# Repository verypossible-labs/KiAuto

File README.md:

KiAuto
======

KiCad automation scripts.
In particular to automate tasks that can't be done using the KiCad native Python interface.
The automation is carried out emulating the user interaction.

## Index

* [Introduction](#introduction)
* [Installation](#installation)
  * [Dependencies](#dependencies)
  * [No installation](#no-installation)
  * [Installation using pip](#installation-using-pip)
  * [Python style installation](#python-style-installation)
  * [Installation on Ubuntu/Debian](#installation-on-debian)
* [Usage](#usage)
  * [Export a schematic to PDF or SVG](#export-a-schematic-to-pdf-or-svg)
  * [Run ERC](#run-erc)
  * [Generate netlist](#generate-netlist)
  * [Update BoM XML or basic BoM generation](#update-bom-xml-or-basic-bom-generation)
  * [Run DRC](#run-drc)
  * [Export layout as PDF](#export-layout-as-pdf)
  * [Refilling copper zones](#refilling-copper-zones)
  * [Common options](#common-options)
  * [Ignoring warnings and errors from ERC or DRC](#ignoring-warnings-and-errors-from-erc-or-drc)
* [History](#history)

## Introduction

Current implementation uses a virtual X server ([xvfb](https://www.x.org/releases/X11R7.6/doc/man/man1/Xvfb.1.xhtml)),
sends key events and detects which window is focused using [xdotool](https://github.com/jordansissel/xdotool/)
and handles the clipboard using [xclip](https://github.com/astrand/xclip).
This means it works for Linux. KiCad is also available for Windows and MacOSX, help to port the scripts will be appreciated.

Currently tested and working:

- Exporting schematics to PDF, SVG, PS, DXF and HPGL
- Exporting layouts (PCBs) to PDF
- Running ERC on schematics
- Running DRC on layouts
- Netlist generation
- Basic BoM generation (mainly the XML needed for [KiBoM](https://github.com/SchrodingersGat/KiBoM))

If you are looking for Gerbers, Drill, Position, STEP and more take a look at [KiBot](https://github.com/INTI-CMNB/KiBot).

This project started as a fork of [kicad-automation-scripts](https://github.com/obra/kicad-automation-scripts) for more information read the [history](#History) section.

A docker image containg the scripts and other tools can be found at [DockerHub](https://hub.docker.com/repository/docker/setsoft/kicad_auto).

## Installation

### Dependencies

If you are installing from a Debian package you don't need to worry about dependencies, otherwise you need to install:

- [**KiCad**](http://kicad-pcb.org/) 5.1.x
- [**xdotool**](https://github.com/jordansissel/xdotool)
- [**xclip**](https://github.com/astrand/xclip)
- [**xsltproc**](http://xmlsoft.org/xslt/) (usually installed as a KiCad dependency). Only needed for BoMs.

If you want to debug problems you could also need:

- [**recordmydesktop**](http://recordmydesktop.sourceforge.net/about.php), to create a video of the KiCad session.
- [**x11vnc**](http://www.karlrunge.com/x11vnc/) and a client like [**ssvnc**](http://www.karlrunge.com/x11vnc/ssvnc.html), to see the KiCad live interaction.
- [**fluxbox**](http://fluxbox.org/) and [**wmctrl**](http://tripie.sweb.cz/utils/wmctrl/) if you want to have a window manager when using **x11vnc**. Othewise windows can't be moved.

### Installation using pip

```shell
pip install kiauto
```

You can also install the current git code running:

```shell
pip install .
```

In the root of the repo.

### Python style installation

Just run the setup, like with any other Python tool:

```
sudo python3 setup.py install
```

### No installation

You can use the scripts without installing. The scripts are located at the *src/* directory.

You can also define bash aliases:

```
alias pcbnew_do=PATH_TO_REPO/src/pcbnew_do
alias eeschema_do=PATH_TO_REPO/src/eeschema_do
```

Note that the following Python 3 packages must be installed:

- [**xvfbwrapper**](https://pypi.org/project/xvfbwrapper/)
- [**psutil**](https://pypi.org/project/psutil/)

Also note that this won't work if you plan to call the scripts from KiBot or other tool.
Aliases are good for direct command line use, but are restricted to the shell where the aliases are declared.
You can add the aliases to the bash configuration, but if the tool doesn't use bash or don't even use a shell this won't work.

### Installation on Debian

Get the Debian package from the [releases section](https://github.com/INTI-CMNB/KiAuto/releases) and run:
```
sudo apt install ./kiauto_*_all.deb
```

## Usage

Two scripts are provided:

- **eeschema_do**: interacts with KiCad's eeschema (schematic editor)
- **pcbnew_do**: interacts with KiCad's pcbnew (PCB editor)

You can get detailed help using the *--help* command line option. Here I include some basic usage.

### Export a schematic to PDF or SVG

```
eeschema_do export -a YOUR_SCHEMATIC.sch DESTINATION/
```
This will create *DESTINATION/YOUR_SCHEMATIC.pdf* file containing all the schematic pages. If you want just one page remove the *-a* option. If you want an SVG file just use *-f svg* like this:
```
eeschema_do export -a -f svg YOUR_SCHEMATIC.sch DESTINATION/
```
In this case you'll get one SVG for each page in your schematic.

### Run ERC

To run the Electrical Rules Check:
```
eeschema_do run_erc YOUR_SCHEMATIC.sch DESTINATION/
```
If an error is detected you'll get a message and the script will return a negative error level. Additionally you'll get *DESTINATION/YOUR_SCHEMATIC.erc* containing KiCad's report.

### Generate netlist

To generate or update the netlist, needed by other tools:
``` 
eeschema_do netlist YOUR_SCHEMATIC.sch DESTINATION/
```
You'll get *DESTINATION/YOUR_SCHEMATIC.net*

### Update BoM XML or basic BoM generation:

Tools like [KiBoM](https://github.com/SchrodingersGat/KiBoM) can generate a nice BoM, but in order to run them from the command line you need to be sure that the project's XML BoM is updated. You can do it running:
``` 
eeschema_do bom_xml YOUR_SCHEMATIC.sch DESTINATION/
```
After running it *./YOUR_SCHEMATIC.xml* will be updated. You'll also get *DESTINATION/YOUR_SCHEMATIC.csv* contain a very basic BoM generated using KiCad's *bom2grouped_csv.xsl* template.

### Run DRC

To run the Distance Rules Check:
```
pcbnew_do run_drc YOUR_PCB.kicad_pcb DESTINATION/
```
If an error is detected you'll get a message and the script will return a negative error level. Additionally you'll get *DESTINATION/drc_result.rpt* containing KiCad's report. You can select the name of the report using *--output_name* and you can ignore unconneted nets using *--ignore_unconnected*.

### Export layout as PDF

This is useful to complement your gerber files including some extra information in the *Dwgs.User* or *Cmts.User* layer.
```
pcbnew_do export YOUR_PCB.kicad_pcb DESTINATION/ LAYER1 LAYER2
```
Will generate *DESTINATION/printed.pdf* containing LAYER1 and LAYER2 overlapped. You can list as many layers as you want. I use things like ```F.Cu Dwgs.User```. The name of the layers is the same you see in the GUI, if your first inner layer is GND you just need to use ```GND.Cu```.

If you need to get a list of valid layers run:

```
pcbnew_do export --list YOUR_PCB.kicad_pcb
```

### Refilling copper zones

When you run the DRC KiCad will refill all zones. If you didn't do it before saving it could lead to a situation where the PCB that passes DRC isn't the one saved to disk. To solve you can use *-s* option to save the PCB after DRC:

```
pcbnew_do run_drc -s YOUR_PCB.kicad_pcb DESTINATION/
```

Another option could be to avoid changing the file on disk, but fill the zones before printing. To achieve it you can invoke the export command like this:

```
pcbnew_do export -f YOUR_PCB.kicad_pcb DESTINATION/ LAYERs...
```

### Common options

By default all the scripts run very quiet. If you want to get some information about what's going on use *-v*. 

The nature of these scripts make them very fragile. In particular when you run them in your every day desktop. You must avoid having *eeschema* and/or *pcbnew* windows opened while running the scripts. If you need to debug a problem you can:
1. Use the *-vv* option to get debug information
2. Use the *-r* option to record a video (OGV format) containing the GUI session. The file will be stored in the output directory and its name will begin with the name of the requested command.
3. Use the *-s* and *-w* options to start **x11vnc**. The execution will stop asking for a keypress. At this time you can start a VNC client like this: ```ssvncviewer :0```. You'll be able to see KiCad running and also interact with it.
4. Same as 3 but also using *-m*, in this case you'll get a window manager to move the windows and other stuff.

### Ignoring warnings and errors from ERC or DRC

Sometimes we need to ignore some warnings and/or errors reported during the ERC and/or DRC test.

To achieve it you need to create a *filters file*. Each line contains a rule to exclude one or more matching errors. The syntax is:

```
ERROR_NUMBER,REGULAR_EXPRESSION
```

The regular expression must follow the Python syntax. In the simplest case this can be just the text that the error must contain.

The error number is just the KiCad internal number for the error you want to ignore.

Here is an example, suppose our report says:

```
** Created on 2020-06-05 11:16:21 **

** Found 2 DRC errors **
ErrType(45): Courtyards overlap
    @(144.361 mm, 101.752 mm): Footprint C16 on F.Cu
    @(144.825 mm, 101.244 mm): Footprint C19 on F.Cu
ErrType(45): Courtyards overlap
    @(159.885 mm, 97.663 mm): Footprint R4 on F.Cu
    @(160.393 mm, 97.191 mm): Footprint C21 on F.Cu

** Found 0 unconnected pads **

** End of Report **
```

Here we have two errors, both number 45. So lets suppose we want to ignore the first error, we could use the following filter:

```
45,Footprint C16
```

This will ignore any error of type 45 (Courtyards overlap) related to *Footprint C16*. To use
it you just need mto use the *-f* command line option:

```
pcbnew_do run_drc -f FILTER_FILE YOUR_PCB.kicad_pcb DESTINATION/
```

Note that when using KiCad 6 the errors are strings enclosed by brackets, use only the text, not the brackets.

## History

I saw a presentation of Jesse Vincent ([@obra](https://github.com/obra)) in the [KiCon 2019](https://2019.kicad-kicon.com/) about automating KiCad tasks.

The presentation used [kicad-automation-scripts](https://github.com/obra/kicad-automation-scripts) as base for the tasks that needs to emulate the user interaction.
So I forked this repo.

But this wasn't the original repo, Jesse's repo is a fork of Productize SPRL's [scripts](https://github.com/productize/kicad-automation-scripts).
These scripts were created by Seppe Stas ([@seppestas](https://github.com/seppestas)).

According to Seppe he took many ideas from the [split-flap display project](https://scottbez1.github.io/splitflap/).
In particular from the files [here](https://github.com/scottbez1/splitflap/tree/master/electronics/scripts).
The author of split-flap is Scott Bezek ([@scottbez1](https://github.com/scottbez1)).
Scott explained the idea in his [blog](https://scottbezek.blogspot.be/2016/04/scripting-kicad-pcbnew-exports.html)

So this is the history of the scripts, at least what I know. In short: Scott Bezek had the original idea and used it for his project, but not as a separated tool.
Seppe Stas from Productize SPRL took the scripts and created a tool from them.
Then Jesse Vincent used the scripts to create a bigger set of tools and presented it on KiCon 2019.
And finally I (Salvador E. Tropea) took Jesse's scripts and adapted them to the needs of [KiBot](https://github.com/INTI-CMNB/KiBot).

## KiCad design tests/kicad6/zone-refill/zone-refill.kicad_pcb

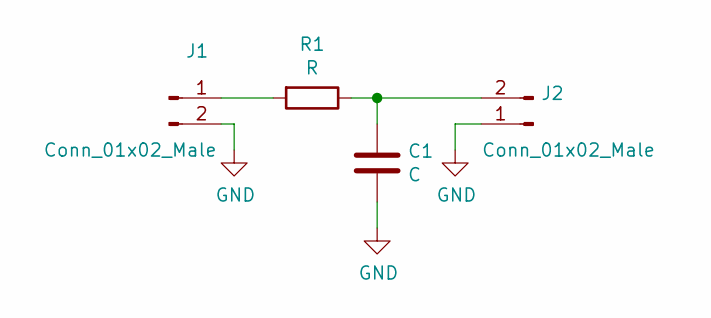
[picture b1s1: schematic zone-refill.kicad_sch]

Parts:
C1: C; C_0805_2012Metric
J1, J2: Conn_01x02_Male; PinHeader_1x02_P2.54mm_Vertical
R1: R; R_0805_2012Metric

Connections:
GND: C1.2, J1.2, J2.1
unnamed: C1.1, J2.2, R1.1
unnamed: J1.1, R1.2

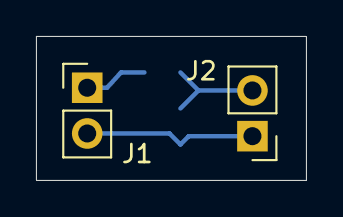
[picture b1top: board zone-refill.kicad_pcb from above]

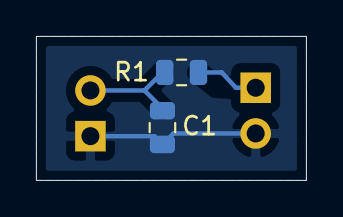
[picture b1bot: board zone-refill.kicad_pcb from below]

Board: 2 copper layers, 15.0 x 8.0 mm, 4 parts (2 on the bottom side), 3 nets.

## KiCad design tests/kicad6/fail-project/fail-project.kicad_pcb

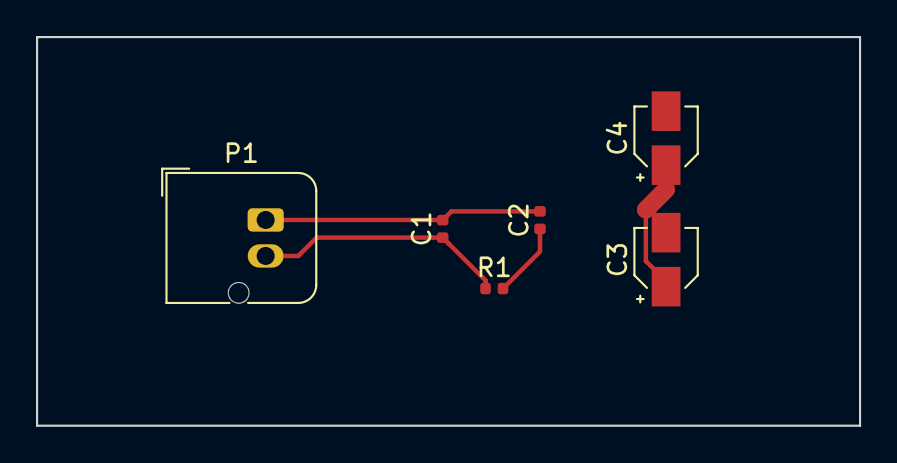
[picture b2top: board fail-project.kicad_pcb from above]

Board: 2 copper layers, 45.7 x 21.6 mm, 6 parts (0 on the bottom side), 5 nets.

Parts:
C1, C2: C; C_0402_1005Metric
C3, C4: CP; CP_Elec_3x5.3
P1: CONN_01X02; JST_JWPF_B02B-JWPF-SK-R_1x02_P2.00mm_Vertical
R1: R; R_0402_1005Metric

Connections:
/Power/VCC: C1.1, P1.2, R1.1
GND: C1.2, C2.2, P1.1
unnamed: C2.1, R1.2
unnamed: C3.1, C4.1
unnamed: C3.2, C4.2

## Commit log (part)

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2019-04-10 Disable the "rescue" dialog on schematic open
2019-04-10 Switch to building our Dockerfile directly, rather than using productize' intermediate version
2019-04-10 switch to the current way to trigger plotting "Alt-f l"
2019-04-10 Update Dockerfile to include license and content from the previous intermediate Dockerfile
2019-04-10 port schematic output to KiCAD 5.1
2019-04-11 A first pass at a working BOM generator
2019-04-18 reorder the library warning to later, since that's whne it seems to run
2020-03-04 Modified to be run outside docker: 1) Language set as english + UTF-8 2) Saves the current pcbnew config and creates one usable. Te original is restored.
2020-03-04 util/ui_automation.py: - recorded_xvfb now can be used without recording - added wait_focused and wait_not_focused - added slip_id parameter to wait_for_window to differentiate two windows with the s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
2020-03-04 schematic.py: - Disabled long waits to test for old errors. - Made stronger the eeschema config parser. - Simplified the calls to recorded_xvfb/Xvfb (now recorded_xvfb can be used without recording) 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
2020-03-04 _pcbnew/run_drc.py: suppressed the pcbnew stderr (noissy)
2020-03-04 _pcbnew/run_drc.py: added width and height config for the record function.
2020-03-05 Added a test (and wait) for the Xvfb, sometimes is slow and xclip runs before it. Also supressed the recordmydesktop output.
2020-03-06 Unified the loggers and made it coloured
2020-03-06 Simplified the log format for information. Remove colors when stderr is a file.
2020-03-06 Adjusted the logger colors
2020-03-06 Renamed _pcbnew/run_drc.py to src/pcbnew_run_drc.py
2020-03-06 Adapted print_layers.py to the same functionality used in run_drc
2020-03-06 Fixed src/pcbnew* always recorded the session
2020-03-06 MAde schematic and output_dir position args (always used)
2020-03-09 Now we also replace kicad_common, to configure /bin/cat as editor.
2020-03-09 Now we keep only the last recorded video.
2020-03-09 Simplified the BOM_XML sequence messages and calls.
2020-03-09 Fixed file format selection for export
2020-03-09 Greater delay in the create files poll.
2020-03-09 Moved the eeschema/export_bom.py functionality to the bom_xml command of src/eeschema_do.py
2020-03-09 Removed _pcbnew/generate_svg.py, its functionality can be achieved using pcbnew_print_layers.py
2020-03-09 Removed custom configs. Now they are generated on-the-fly.
2020-03-10 Removed KiCad back-ups from the tests directory.
2020-03-10 Added Apache 2.0 license text
2020-03-10 Changed error level of src/pcbnew_run_drc to negative to be more coherent with the run_erc command.
2020-03-10 Added option to list all layers to pcbnew_print_layers
2020-03-10 Added the READMe.md to the Debian package.
2020-03-16 Bumped version to 1.1.0.
2020-03-19 Bumped version to 1.1.1
2020-03-21 Bumped version to 1.1.2
2020-03-30 Bumped version to 1.1.3
2020-04-20 Support missing *-lib-table in user config
2020-04-20 Now eeschema_do reports ERC warnings as warning messages
2020-04-20 Bumped version to 1.1.5
2020-04-30 Removed kicad-ppa.pgp, no longer used.
2020-04-30 Imported kicad5/fail-project with KiCad 5.1.5
2020-04-30 Removed KiCad 4 and redundante test
2020-04-30 Made flake8 compliant
2020-05-01 Added tests for pcbnew_run_drc
2020-05-01 Added 4 layers and comments in Dwgs and Cmts to the "good" test
2020-05-02 Fixed compare_txt, wasn't really working
2020-05-02 Added a changelog
2020-05-02 Added support for eeschema to the TestContext class
2020-05-02 Simplified the way I pass the test_dir to the tests
2020-05-03 Added "eeschema_do export" tests
2020-05-03 Fixed typo in CI pipeline config
2020-05-03 Added coverage to the test process.
2020-05-04 Added coveralls script to collect coverage data.
2020-05-04 Still having problems with coveralls, added debug to meassure the token
2020-05-04 Another test for coveralls
2020-05-04 Added badgets to the README.md
2020-05-05 Using subprocess.DEVNULL instead of opening /dev/null
2020-05-05 Fixed missing arguments and imports (Oops!)
2020-05-05 Added test for the case when pcbnew is already running.
2020-05-07 Moved the functionality of pcbnew_run_drc to pcbnew_do- Adapted the tests.
2020-05-07 Fixed comment about what is tested, now is pcbnew_do
2020-05-07 Made actions run on all branches.
2020-05-07 Commented unused functions on eeschema_do
2020-05-07 Added reference output for postscript
2020-05-07 Updated the changelog
2020-05-08 Increased file creation default timeout
2020-05-08 Added code to preserve the project file during eeschema operations.
2020-05-08 Ignore back-ups on good-project
2020-05-08 Commented some tests
2020-05-08 Added tests for the case when a previous run failed catastrophically and left back-ups.
2020-05-08 Added xprop output before raising RuntimeError to improbe debugging
2020-05-08 During sch export we wait for eeschema to exit, if it doesn't we re try and if it still not reponding we kill it.
2020-05-08 Added test for inner layer names in kiplot style
2020-05-09 Modified Coveralls URL
2020-05-11 Added missing 3D model for good-project.kicad_pcb, copied KiCad 3D models to a local dir, to make the project independent.
2020-05-11 Added more installation options.
2020-05-11 Removed redundant log message
2020-05-12 Enable the code for "Remap symbols" (KiCad 4 SCH). Added test and optimized the start-up wait when other windows pop-up instead of the main window.
2020-05-12 Added test for run_drc --save
2020-05-12 Changed the default zone-refill PCB
2020-05-12 Excluded from coverage the ui_automation.py debug_window code.
2020-05-13 Excluded the pythonapp.yml workflow from tags starting with "v"
2020-05-13 Bumped version to 1.2.0.
2020-05-18 Changed default recording height to 960
2020-05-18 Added test to cover the WM and x11vnc code.
2020-05-18 Updated the changelogs
2020-05-18 Eliminated the files filter for the Python pipeline
2020-05-18 Added python filters to pythonapp.yml workflow
2020-05-19 Fixed: under some situations the EEschema plot dialog failed to clear the old file path and we pasted concatenated. Was introduced when fixing the browse button selected.
2020-05-24 Some times when exiting xdotool didn't find any window and reported error.
2020-06-05 DRC errors and warnings are now reported
    They are logged as error/warning messages so you do not need to consult the
    report.
2020-06-05 Fixed: error when using export (no filters there)
2020-06-06 Added "error filter" feature to the changelog.
2020-06-06 Added a test case for a filter file.
2020-06-08 Now we always close the DRC dialog.
2020-06-08 Added a test case for the PCB recovery feature.
2020-06-08 Added a test for a multi-file export with partial overwrite
2020-06-11 Added more information about what is filtered
    - Filtered errors are displayed as warnings, but ignored.
    - Filtered warnings are displayed as information.
    - When an error/warning is filtered a debug message informs which regex matched.
2020-06-14 Added option to fill zones before printing in pcbnew_do
2020-06-14 Bumped version to 1.4.1
2020-09-09 Added a wait point in pcbnew_do
    Is when it fails to get the main pcbnew window.
    Right before trying to get rid of a dialog.
2020-09-09 Fixed flake8 deetails
2020-09-09 Fixed the --warnings_as_errors output.
    As @ottojo points in #1 this option counted warnings as errors, but
    never printed the warnings.
    Now the code does what the option says: warnings are converted to
    errors. Not just counted as errors, but also printed as errors.
    I think this is more coherent with the name of the option.
2020-09-13 Made test the local test, the server side is never used.
2020-09-13 Added support to run eeschema-nightly
    - Also added support to KiCad 5.99 ERC
    - Added a Config class to put all configuration values together
2020-09-14 Modified the "good" DRC test to be good for KiCad 6
2020-09-14 Fixed the case when we detect an error while creating a new config.
    In this case we have a back-up, but no new file.
2020-09-15 Added pcbnew_do export support to KiCad 5.99
2020-09-15 Added eeschema_do export support for KiCad 5.99
2020-09-15 Unified the output name handling.
2020-09-15 Unified the exit mechanism
    Always using the same path.
2020-09-16 Added KiCad 6 versions of the test projects
2020-09-16 Enabled "test_all_track_errors" option in the DRC.
2020-09-17 Fixed eeschema 5.99 window title regex
2020-09-17 Added support for the new kicad_pro extension to the tests.
2020-09-17 Adapted the tests to the new output names.
    Also generated more references
2020-09-17 Added support for KiCad nightly to the test_pcb_misc
2020-09-17 Adapted the test*misc tests to support KiCad nightly.
2020-09-17 More changes to the reference generation
2020-09-18 Changed debian package name to kiauto
2020-09-18 Added egg-info dir to the deb_clean target
2020-09-18 Better readme.
    - Added index
    - Clarified some concepts
    - Added a history
2020-09-19 Excluded -bak files (we create them)
2020-09-19 Adapted to KiCad 5.99 nightly 20200916
    Currently the DRC dialog is really unfriendly for us.
    I'm just waiting for the DRC completion using a fixed time.
    - Escape aborts the DRC
    - The Save button is always enabled
    - The messages are removed as soon the DRC finishes
    Can't find a solution.
2020-09-20 Fixed the way we handle the dialogs for KiCad 4 schematics.
    KiCad 6 doesn't needs more confirmations that KiCad 5.
2020-09-20 Trying to adapt the filter tests.
    But today a new bug in KiCad nightly was introduced:
    Is impossible to distinguish ERC warnings from errors :-(
2020-09-22 Added KiCad nightly test workflow
2020-09-22 Added target to run docker nightly image.
    Also added reference generation disabling the color scheme.
2020-09-22 Increased verbosity for tests failing on GitHub but not in my machine.
2020-09-23 Support more than one error dialog on eeschema startup.
    Now we can dismiss the "already running" dialog and then dismiss the
    dialog about symbols remap.
2020-09-23 Removed the HTML coverage generation from the tests.
    This needs extra dependencies and isn't really needed.
2020-09-23 Trying another coveralls mechanism
2020-09-23 Now both tokens
2020-09-24 Only coveralls
2020-09-24 Added more debug information to the tests.
2020-09-24 Added support for the Python DRC API on KiCad 5.99
2020-10-03 Adated the KiCad 6 tests to avoid extra DRC errors.
    Silkscreen over pad is now detected.
2020-10-03 Now KiCad 5.99 Fiil Zones is working.
    Full DRC features from Python!
2020-10-05 Added PyPi publish workflow
2020-10-05 Added PyPi installation instructions
2020-10-08 Added job to trigger docker image creation after a release.
2020-10-08 Added PyPi badge
    Also updated the tests badge
2020-10-12 Added pcbnew_do export --mirror option.
    Only usable for KiCad 6.
    KiCad 5 has a limitation about this setting and doesn't look
    like 5.1.8 will fix it.
2020-10-13 Fixed silk screen text outside board in KiCad 6 test cases.
2020-10-13 Disabled ERC check for library issues.
    KiCad 5.99 is reporting some spurious errors.
2020-10-13 Bumped version to 1.5.2
2020-10-14 Fixed problems when using KiCad 5.99 and projects from KiCad 5.
    Trying to restore a missing kicad_prl
2020-10-15 Added support for KiCad 5.99 DRC/ERC reports.
2020-10-15 Bumped version to 1.5.3
2020-11-05 Adapted to the new ERC dialog.
    - More items, so more tabs.
    - This dialog is broken and the support is weak.
    There is no way to detect the end of the ERC.
    I hope the promissed eeschema python bindings get done (as the
    road map says) and then the ERC can be done from python.
2020-11-21 Implement xdotool actions to export a jpg of the 3d view
2020-11-25 Fixed KiCad 6 warning example.
    Missing PWR_FLG, now detected by nightly.
